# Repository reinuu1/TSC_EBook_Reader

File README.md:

# 📘 TSC_EBook_Reader

## 👨‍💻 Proiect realizat de: DINU Andrei-Marian  
### 📚 Pentru cursul: Teoria Sistemelor de Calcul, 2025  

---

## 🔍 Descriere generală

**OpenBook** este un e-reader open-source, construit în jurul microcontrollerului **ESP32-C6**.  
Acesta dispune de:

- Display **E-Ink 7.5"**
- Baterie **Li-Po**
- Stocare **microSD**
- Senzori de mediu (**BME688**)
- Modul RTC (**DS3231**)

---

## Mapping pini ESP32-C6

| Semnal        | ESP32 Pin | Funcție                      |
|---------------|-----------|------------------------------|
| EPD_BUSY      | IO3       | Status display               |
| EPD_RST       | IO23      | Reset display                |
| EPD_DC        | IO5       | Data/Command                 |
| EPD_CS        | IO10      | SPI CS pentru e-paper        |
| EPD_CLK       | IO6       | SPI Clock                    |
| EPD_MOSI      | IO7       | SPI Data Out                 |
| SS_SD         | IO4       | SD Card CS                   |
| SD_MISO       | IO2       | SPI MISO                     |
| I2C_SDA       | IO21      | RTC + BME688                 |
| I2C_SCL       | IO22      | RTC + BME688                 |
| RTC_RST       | IO18      | Reset DS3231                 |
| RTC_INT       | IO0       | Interrupt RTC                |
| 32KHz_CLK     | IO1       | Oscilator RTC                |
| IO/BOOT Btn   | IO9       | Boot                         |
| IO/CHANGE Btn | IO15      | Navigare                     |
| RESET         | EN        | Reset MCU                    |

## Microcontroller: ESP32-C6-WROOM-1

- **Arhitectură:** RISC-V 32-bit @ 160 MHz  
- **Memorie:** 320KB ROM, 512KB SRAM  
- **Conectivitate:** Wi-Fi 6 (2.4GHz), Bluetooth 5.0  
- **Consum:** ~10mA activ, ~160μA deep sleep  

**Interfețe utilizate:**
- **SPI** – e-paper, microSD, memorie Flash
- **I2C** – RTC, senzor de mediu
- **GPIO** – butoane, LED, semnale control

## 🖥️ Display: Waveshare 7.5" e-Ink V2

- **Rezoluție:** 800x480 px  
- **Interfață:** SPI  
- **Consum:** ~1.2mW activ, ~0.1mW standby

## 🔋 Alimentare

- **Baterie:** Li-Po 1800–2500mAh  
- **Încărcător:** MCP73831  
- **Regulator:** XC6221 LDO 3.3V  

**Protecții integrate:**

- Diodă Schottky – polaritate inversă  
- Varistor ESD – protecție USB  
- Supercapacitor – buffering boot/flash  

**Conectare la ESP32-C6:**

IO7 → MOSI
IO6 → SCK
IO10 → CS
IO5 → DC
IO23 → RST
IO3 → BUSY

## Stocare: MicroSD + SPI Flash
### microSD (până la 32GB FAT32)

IO4 → CS_SD
IO2 → MISO
IO7 → MOSI (partajat)
IO6 → SCK (partajat)
Flash SPI externă (Winbond W25Q64JV – 64Mb)
IO11 → CS
IO2, IO6, IO7 partajați

##  Senzor Mediu: Bosch BME688
- Măsoară: temperatură, umiditate, presiune, compuși gazoși  
- **Consum:** ~3.6mA activ, ~0.1μA sleep  
- **Interfață:** I2C  

**Conectare:**

IO21 → SDA
IO22 → SCL
IO19 → VDDIO (enable senzor)

## RTC: DS3231

- **Precizie:** ±2ppm, compensat termic  
- **Backup:** funcționează pe baterie  
- **Consum:** ~1.5μA backup, ~0.1μA sleep 

**Conectare:**

IO21 → SDA
IO22 → SCL
IO18 → RST
IO0 → INT/SQW
IO1 → 32KHz Clock Out

## ⚡ Estimare consum

| Modul       | Activ (mA) | Sleep (μA) |
|-------------|------------|------------|
| ESP32-C6    | ~10        | ~160       |
| Display     | ~1.2       | ~0.1       |
| microSD     | ~50        | ~10        |
| BME688      | ~3.6       | ~0.1       |
| RTC         | ~0.0015    | ~0.0001    |
| **Total**   | **~65mA**  | **~170μA** |

## Interfață utilizator
- 3 Butoane tactile (TS-1187A):

IO9 → BOOT
IO15 → CHANGE
EN → RESET

- LED status: GPIO + rezistor pull-down  
- Feedback: control simplu via GPIO 

## Alte componente

- **Conector FPC:** Hirose FH34SRJ-24S  
- **Test Pads:** silkscreen pentru depanare  
- **Qwiic/I²C Header:** pentru extensii viitoare 

Observații finale
Toate comunicațiile SPI sunt partajate pe același bus, controlate prin CS separat.

Designul este gândit pentru eficiență energetică și poate funcționa zeci de ore în standby.

Tot sistemul este gândit pentru a fi reproductibil și open-source, ușor de extins cu alte module I²C sau SPI

##  Design Decizii & Trade-offs

-  Alegere ESP32-C6: conectivitate & suport FreeRTOS  
-  E-paper pentru consum redus  
-  Un singur bus SPI (cu CS dedicat pentru SD și e-paper)  
-  GPIO-uri simple pentru butoane

## Debug & Testare

-  Verificare DRC (JLCPCB .dru)  
-  Alimentare testată cu Li-Po + charging  
-  Interfețe SPI & I2C testate cu logic analyzer  
-  Consumul în deep sleep confirmat < 200μA

##  Datasheet-uri & Linkuri componente

|                 Componentă                |                                                     Link Datasheet                                                            |                                                          LINK                                                                           |
|-------------------------------------------|-------------------------------------------------------------------------------------------------------------------------------|-----------------------------------------------------------------------------------------------------------------------------------------|
| USB Connector 112A-TAAR-R03               | [ESP32-C6-WROOM-1](https://www.attend.com.tw/data/download/file/112A-TAAR-R03_Spec.pdf)                                       | [Status display](https://www.digikey.com/en/products/detail/attend-technology/112A-TAAR-R03/17633923)                                   |
| Inductor 68uH (Würth)                     | [7.5" V2 e-Paper](https://www.we-online.com/components/products/datasheet/784373170680.pdf)                                   | [Reset display ](https://eu.mouser.com/ProductDetail/Wurth-Elektronik/784373170680?qs=sGAEpiMZZMv126LJFLh8yzGkpireax1GgDeN9GF1EUQ%3D)   |
| LED Bridgelux                             | [DS3231](https://www.bridgelux.com/sites/default/files/resource_media/DS51_Rev%20F%20Bridgelux%20SMD%203030%20Data%20sheet.pdf)  | [Data/Command](https://www.digikey.com/en/products/detail/bridgelux/BXEM-27E0000-0-000/6618599)                                      |
| Voltage Detector BD5229G                  | [BME688 ](https://fscdn.rohm.com/en/products/databook/datasheet/ic/power/voltage_detector/bd52xxg-e.pdf)                      | [SPI CS pentru e-paper        ](https://www.digikey.com/en/products/detail/rohm-semiconductor/BD5229G-TR/658502)                        |
| Butoane TL3315                            | [XC6221B331MR-G](https://fscdn.rohm.com/en/products/databook/datasheet/ic/power/voltage_detector/bd52xxg-e.pdf)               | [SPI Clock                    ](https://www.digikey.com/en/products/detail/rohm-semiconductor/BD5229G-TR/658502)                        |
| Supercapacitor 0.011F 3.3V                | [MCP73831T-2ACI/OT ](https://mm.digikey.com/Volume0/opasdata/d220001/medias/docus/6537/rev05-CPHCPM.pdf)                      | [SPI Data Out                ](https://www.digikey.com/en/products/detail/seiko-instruments/cph3225a/8692444)                           |
| RTC DS3231SN                              | [LP584174 (1800mAh) ](https://www.analog.com/media/en/technical-documentation/data-sheets/DS3231.pdf)                         | [SD Card CS ](https://www.digikey.com/en/products/detail/analog-devices-inc-maxim-integrated/DS3231SN/1197576)                          |
| Capacitor 0402YD104MAT2A                  | [FH34SRJ-24S-0.5SH(50)](https://eu.mouser.com/datasheet/2/40/cx5r_KGM-3223198.pdf)                                            | [SPI MISO                  ](https://eu.mouser.com/ProductDetail/KYOCERA-AVX/0402YD104MAT2A?qs=4PckX6MNpMErOINbbZj3Cw%3D%3D)            |
| ESP32-C6-WROOM-1-N8                       | [W25Q64JV             ](https://www.espressif.com/sites/default/files/documentation/esp32-c6-wroom-1_wroom-1u_datasheet_en.pdf)  | [RTC + BME688                ](https://www.digikey.com/en/products/detail/espressif-systems/ESP32-C6-WROOM-1-N8/17728866)            |
| Varistor USB PFMF.050.2                   | [Molex 104031-0811     ](https://ro.mouser.com/datasheet/2/358/typ_PFMF-1275918.pdf)                                          | [RTC + BME688               ](https://ro.mouser.com/ProductDetail/Schurter/PFMF.050.2?qs=1auRipcfynCums5v1iucSA%3D%3D)                  |
| DiodA Schottky SD0805S020S1R0             | [USB4110-GF-A           ](https://datasheets.kyocera-avx.com/schottky.pdf)                                                    | [Reset DS3231                ](https://www.digikey.com/en/products/detail/kyocera-avx/sd0805s020s1r0/3749517)                           |
| Senzor BME680                             | [SS14                  ](https://www.bosch-sensortec.com/media/boschsensortec/downloads/datasheets/bst-bme680-ds001.pdf)      | [ Interrupt RTC  ](https://www.digikey.com/en/products/detail/bosch-sensortec/bme680/7401317)                                           |
| Rezistori SMD 0402                        | [PFMF05S050T2          ](https://www.yageo.com/upload/media/product/products/datasheet/rchip/PYu-RC_Group_51_RoHS_L_12.pdf)   | [Oscilator RTC ](https://www.digikey.com/en/products/detail/yageo/RC0402JR-07100KL/726416)                                              |
| P-MOS DMG2305UX-7                         | [TS-1187A-B-A-B        ](https://www.diodes.com/assets/Datasheets/DMG2305UX.pdf)                                              | [Boot                        ](https://www.digikey.com/en/products/detail/diodes-incorporated/DMG2305UX-7/4340667)                      |
| MCP73831T (Charger IC)                    | [RC0402FR-07100KL       ](https://ww1.microchip.com/downloads/en/DeviceDoc/MCP73831-Family-Data-Sheet-DS20001984H.pdf)        | [Navigare   ](https://www.digikey.com/en/products/detail/microchip-technology/MCP73831T-2ACI-OT/964301)                                 |
| Hirose FH34SRJ-24S-0.5SH                  | [GRM155R61A105KE15D    ](https://ro.mouser.com/datasheet/2/185/FH34SRJ_24S_0_5SH_99__CL0580_1255_6_99_2DDrawing_0-1615044.pdf)| [Reset MCU                   ](https://ro.mouser.com/ProductDetail/Hirose-Connector/FH34SRJ-24S-0.5SH99?qs=vcbW%252B4%252BSTIpKBl5ap9J8Fw%3D%3D) |
| Battery Monitor MAX17048                  | https://www.analog.com/media/en/technical-documentation/data-sheets/max17048-max17049.pdf                                     | https://www.digikey.com/en/products/detail/analog-devices-inc-maxim-integrated/MAX17048G-T10/3758921                                    |
| Diodă MBR0530                             | https://ro.mouser.com/datasheet/2/258/MBR0520_MBR0580_SOD123_-2492194.pdf                                                     | https://ro.mouser.com/ProductDetail/Micro-Commercial-Components-MCC/MBR0530-TP?qs=KFo7JewZbUECRHkxGanrdg%3D%3D                          |
| ESD Suppressor – PGB1010603MR             | https://www.littelfuse.com/assetdocs/pulseguard-esd-suppressors-pgb1-datasheet?assetguid=8a337998-d54d-466b-be4e-dc5bcd1f9321 | https://www.digikey.com/en/products/detail/littelfuse-inc/PGB1010603MR/715755                                                           |
| Qwiic Connector OM-E-QWIIC                | https://www.sparkfun.com/qwiic                                                                                                | https://www.digikey.com/en/products/detail/onion-corporation/om-e-qwiic/9922970                                                         |
| Capacitor 0.5pF–100uF GCQ1555C1HR50WB01   | https://ro.mouser.com/datasheet/2/281/1/GCQ1555C1HR50WB01_01A-3146956.pdf                                                     | https://ro.mouser.com/ProductDetail/Murata-Electronics/GCQ1555C1HR50WB01D?qs=0lQeLiL1qybSG%2FOlONlvIA%3D%3D                             |
| USB-C Conector USB4110-GF-A               | https://gct.co/files/drawings/usb4110.pdf                                                                                     | https://eu.mouser.com/ProductDetail/GCT/USB4110-GF-A?qs=KUoIvG%2F9IlYiZvIXQjyJeA%3D%3D                                                  |
| Rezistor                                  | https://industrial.panasonic.com/ww/products/pt/general-purpose-chip-resistors/models/ERJ2GE0R00X                             | https://www.digikey.com/en/products/detail/panasonic-electronic-components/ERJ-2GE0R00X/146727                                          |

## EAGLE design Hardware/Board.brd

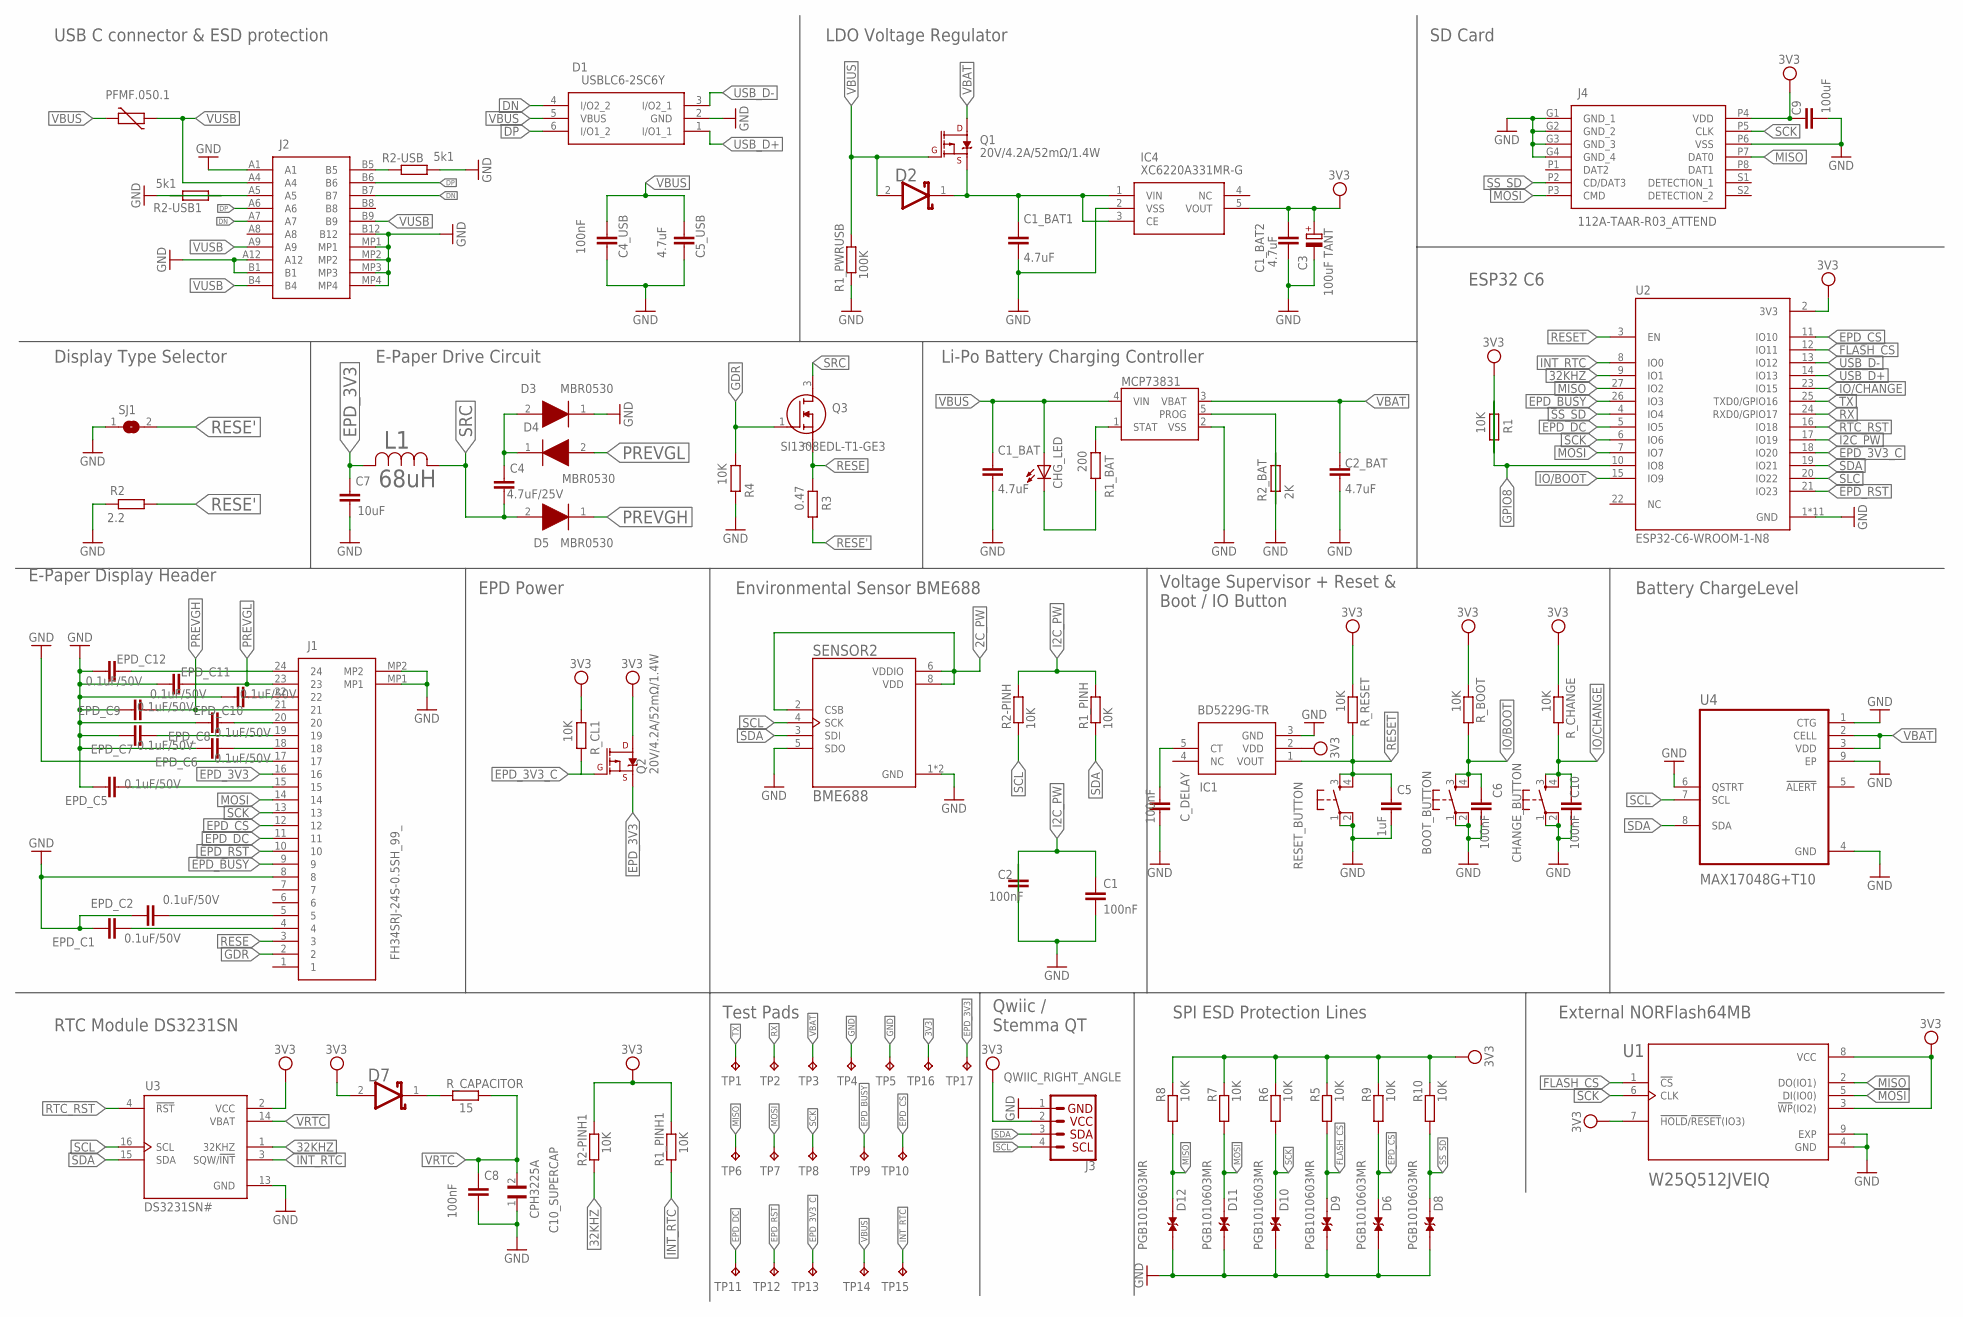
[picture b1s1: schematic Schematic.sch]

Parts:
BOOT_BUTTON: BUTTON_CUSYOMV1; MYBUTTON
C1, C2, C4_USB, C6, C8, C10: 100nF; EAGLE-LTSPICE_C0402
C1_BAT, C1_BAT1, C1_BAT2, C2_BAT, C5_USB: 4.7uF; EAGLE-LTSPICE_C0402
C3: 100uF TANT; RCL_CT3528
C4: 4.7uF/25V; EAGLE-LTSPICE_C0402
C5: 1uF; EAGLE-LTSPICE_C0402
C7: 10uF; EAGLE-LTSPICE_C0402
C9: 100uF; EAGLE-LTSPICE_C0402
C10_SUPERCAP: CPH3225A; CAPCP3225X100N
CHANGE_BUTTON: BUTTON_CUSYOMV1; MYBUTTON
CHG_LED: ADAFRUIT_LEDCHIP-LED0603; ADAFRUIT_CHIP-LED0603
C_DELAY: 100nF; EAGLE-LTSPICE_C0402
D1: USBLC6-2SC6Y; SOT95P280X145-6N
D2, D7: ESP32_WROVER_AVX---SD0805S020S1R0_AVX_SD0805S020S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; ESP32_WROVER_AVX---SD0805S020S1R0_AVX_SD0805S020S1R0_0
D3, D4, D5: MBR0530; SOD3716X135N
D6, D8, D9, D10, D11, D12: PGB1010603MR; DIOC1608X36N
EPD_C1, EPD_C2, EPD_C5, EPD_C6, EPD_C7, EPD_C8, EPD_C9, EPD_C10, EPD_C11, EPD_C12: 0.1uF/50V; EAGLE-LTSPICE_C0402
IC1: BD5229G-TR; SOT95P280X125-5N
IC4: XC6220A331MR-G; SOT95P280X120-5N
J1: FH34SRJ-24S-0.5SH_99_; FH34SRJ24S05SH99
J2: J2; SAMACSYS_PARTS_USB4110GFA
J3: QWIIC_RIGHT_ANGLE; JST04_1MM_RA
J4: 112A-TAAR-R03_ATTEND; 112ATAARR03ATTEND
L1: 68uH; IND_4828-WE-TPC_WRE
MCP73831: ESP32_WROVER_SPARKFUN-IC-POWER_MCP73831; ESP32_WROVER_SPARKFUN-IC-POWER_SOT23-5
PFMF.050.1: ESP32C6_VARISTORCN1812; ESP32C6_VARISTOR_CT/CN1812
Q1, Q2: 20V/4.2A/52mΩ/1.4W; ESP32_WROVER_SPARKFUN-DISCRETESEMI_SOT23-3
Q3: SI1308EDL-T1-GE3; SOT65P210X110-3N
R1, R1_PINH, R1_PINH1, R2-PINH, R2-PINH1, R4, R5, R6, R7, R8, R9, R10: 10K; ESP32_WROVER_EAGLE-LTSPICE_R0402
R1_BAT: 200; ESP32_WROVER_EAGLE-LTSPICE_R0402
R1_PWRUSB: 100K; ESP32_WROVER_EAGLE-LTSPICE_R0402
R2: 2.2; ESP32_WROVER_EAGLE-LTSPICE_R0402
R2-USB, R2-USB1: 5k1; ESP32_WROVER_EAGLE-LTSPICE_R0402
R2_BAT: 2K; ESP32_WROVER_EAGLE-LTSPICE_R0402
R3: 0.47; ESP32_WROVER_EAGLE-LTSPICE_R0402
RESET_BUTTON: BUTTON_CUSYOMV1; MYBUTTON
R_BOOT: 10K; ESP32_WROVER_EAGLE-LTSPICE_R0402
R_CAPACITOR: 15; ESP32_WROVER_EAGLE-LTSPICE_R0402
R_CHANGE: 10K; ESP32_WROVER_EAGLE-LTSPICE_R0402
R_CL1: 10K; ESP32_WROVER_EAGLE-LTSPICE_R0402
R_RESET: 10K; ESP32_WROVER_EAGLE-LTSPICE_R0402
SENSOR2: BME688; ESP32_WROVER_BME680_PSON80P300X300X100-8N
SJ1: SJ
TP1, TP2, TP3, TP4, TP5, TP6, TP7, TP8, TP9, TP10, TP11, TP12, TP13, TP14, TP15, TP16, TP17: TPTP20R; TP20R
U1: W25Q512JVEIQ; SON127P600X800X80-9N
U2: ESP32-C6-WROOM-1-N8; XCVR_ESP32-C6-WROOM-1-N8
U3: DS3231SN#; SOIC127P1032X265-16N
U4: MAX17048G+T10; SON50P200X200X80-9N

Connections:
2C_PW: SENSOR2.2 (CSB), SENSOR2.6 (VDDIO), SENSOR2.8 (VDD)
3V3: C1_BAT2.2, C3.+, C9.2, D7.2 (ANODE), IC1.2 (VDD), IC4.5 (VOUT), J3.2, J4.P4 (VDD), Q2.3 (D), R1.1, R1_PINH1.2, R2-PINH1.2, R5.2, R6.2, R7.2, R8.2, R9.2, R10.2, R_BOOT.1, R_CHANGE.1, R_CL1.2, R_RESET.1, TP16.TP, U1.3 (!WP!(IO2)), U1.7 (!HOLD!/!RESET!(IO3)), U1.8 (VCC), U2.2 (3V3), U3.2 (VCC)
32KHZ: R2-PINH1.1, U2.9 (IO1), U3.1 (32KHZ)
DN: J2.A7
DP: J2.A6
EPD_3V3: C7.1, J1.16, L1.2, Q2.2 (S), TP17.TP
EPD_3V3_C: Q2.1 (G), R_CL1.1, TP13.TP, U2.18 (IO20)
EPD_BUSY: J1.9, TP9.TP, U2.26 (IO3)
EPD_CS: D6.2, J1.12, R9.1, TP10.TP, U2.11 (IO10)
EPD_DC: J1.11, TP11.TP, U2.5 (IO5)
EPD_RST: J1.10, TP12.TP, U2.21 (IO23)
FLASH_CS: D9.2, R5.1, U1.1 (!CS), U2.12 (IO11)
GDR: J1.2, Q3.1 (G), R4.2
GND: BOOT_BUTTON.1, BOOT_BUTTON.2, C1.2, C1_BAT.1, C1_BAT1.1, C1_BAT2.1, C2.2, C2_BAT.1, C3.-, C4_USB.2, C5.2, C5_USB.2, C6.2, C7.2, C8.2, C9.1, C10.2, C10_SUPERCAP.1, CHANGE_BUTTON.1, CHANGE_BUTTON.2, C_DELAY.2, D1.2 (GND), D3.1 (K), D6.1, D8.1, D9.1, D10.1, D11.1, D12.1, EPD_C1.1, EPD_C2.1, EPD_C5.1, EPD_C6.1, EPD_C7.1, EPD_C8.1, EPD_C9.1, EPD_C10.1, EPD_C11.1, EPD_C12.1, IC1.3 (GND), IC4.2 (VSS), J1.8, J1.17, J1.MP1, J1.MP2, J2.A1, J2.A12, J2.B1, J2.B12, J2.MP1, J2.MP2, J2.MP3, J2.MP4, J3.1, J4.G1 (GND_1), J4.G2 (GND_2), J4.G3 (GND_3), J4.G4 (GND_4), J4.P6 (VSS), MCP73831.2 (VSS), R1_PWRUSB.1, R2.2, R2-USB.2, R2-USB1.1, R2_BAT.1, R4.1, RESET_BUTTON.1, RESET_BUTTON.2, SENSOR2.1 (GND), SENSOR2.5 (SDO), SENSOR2.7 (GND), SJ1.1, TP4.TP, TP5.TP, U1.4 (GND), U1.9 (EXP), U2.1 (GND), U2.28 (GND), U2.29_1 (GND), U2.29_2 (GND), U2.29_3 (GND), U2.29_4 (GND), U2.29_5 (GND), U2.29_6 (GND), U2.29_7 (GND), U2.29_8 (GND), U2.29_9 (GND), U3.13 (GND), U4.1 (CTG), U4.4 (GND), U4.6 (QSTRT), U4.9 (EP)
GPIO8: R1.2, U2.10 (IO8)
I2C_PW: R1_PINH.2, R2-PINH.2, U2.17 (IO19)
INT_RTC: R1_PINH1.1, TP15.TP, U2.8 (IO0), U3.3 (SQW/!INT)
IO/BOOT: BOOT_BUTTON.3, BOOT_BUTTON.4, C6.1, R_BOOT.2, U2.15 (IO9)
IO/CHANGE: C10.1, CHANGE_BUTTON.3, CHANGE_BUTTON.4, R_CHANGE.2, U2.23 (IO15)
MISO: D12.2, J4.P7 (DAT0), R8.1, TP6.TP, U1.2 (DO(IO1)), U2.27 (IO2)
MOSI: D11.2, J1.14, J4.P3 (CMD), R7.1, TP7.TP, U1.5 (DI(IO0)), U2.7 (IO7)
unnamed: J2.A5, R2-USB1.2
unnamed: J2.B5, R2-USB.1
unnamed: C4_USB.1, C5_USB.1
unnamed: C4.1, D3.2 (A), D4.1 (K)
unnamed: MCP73831.1 (STAT), R1_BAT.2
unnamed: C1_BAT1.2, D2.1 (CATHODE), IC4.1 (VIN), IC4.3 (CE), Q1.2 (S)
unnamed: CHG_LED.C, R1_BAT.1
unnamed: EPD_C12.2, J1.24
unnamed: MCP73831.5 (PROG), R2_BAT.2
unnamed: C1.1, C2.1
unnamed: C_DELAY.1, IC1.5 (CT)
unnamed: D7.1 (CATHODE), R_CAPACITOR.1
unnamed: EPD_C10.2, J1.22
unnamed: EPD_C8.2, J1.20
unnamed: EPD_C7.2, J1.19
unnamed: EPD_C6.2, J1.18
unnamed: EPD_C5.2, J1.15
unnamed: EPD_C2.2, J1.5
unnamed: EPD_C1.2, J1.4
PREVGH: D5.1 (K), EPD_C9.2, J1.21
PREVGL: D4.2 (A), EPD_C11.2, J1.23
RESE: J1.3, Q3.2 (S), R3.2
RESE': R3.1, SJ1.2
RESET: C5.1, IC1.1 (VOUT), RESET_BUTTON.3, RESET_BUTTON.4, R_RESET.2, U2.3 (EN)
RTC_RST: U2.16 (IO18), U3.4 (!RST)
RX: TP2.TP, U2.24 (RXD0/GPIO17)
SCK: D10.2, J1.13, J4.P5 (CLK), R6.1, TP8.TP, U1.6 (CLK), U2.6 (IO6)
SCL: J3.4, R2-PINH.1, SENSOR2.4 (SCK), U3.16 (SCL), U4.7 (SCL)
SDA: J3.3, R1_PINH.1, SENSOR2.3 (SDI), U2.19 (IO21), U3.15 (SDA), U4.8 (SDA)
SLC: U2.20 (IO22)
SRC: C4.2, D5.2 (A), L1.1, Q3.3 (D)
SS_SD: D8.2, J4.P2 (CD/DAT3), R10.1, U2.4 (IO4)
TX: TP1.TP, U2.25 (TXD0/GPIO16)
USB_D+: D1.1 (I/O1_1), U2.14 (IO13)
USB_D-: D1.3 (I/O2_1), U2.13 (IO12)
VBAT: C2_BAT.2, MCP73831.3 (VBAT), Q1.3 (D), TP3.TP, U4.2 (CELL), U4.3 (VDD)
VBUS: C1_BAT.2, CHG_LED.A, D2.2 (ANODE), MCP73831.4 (VIN), PFMF.050.1.2, Q1.1 (G), R1_PWRUSB.2, TP14.TP
VRTC: C8.1, C10_SUPERCAP.2, R_CAPACITOR.2, U3.14 (VBAT)
VUSB: J2.A4, PFMF.050.1.1

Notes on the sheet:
USB C connector & ESD protection
Display Type Selector
E-Paper Drive Circuit
LDO Voltage Regulator
SD Card
Li-Po Battery Charging Controller
ESP32 C6
E-Paper Display Header
EPD Power
Environmental Sensor BME688
Voltage Supervisor + Reset & Boot / IO Button
Battery ChargeLevel
External NORFlash64MB
RTC Module DS3231SN
Test Pads
Qwiic / Stemma QT
SPI ESD Protection Lines

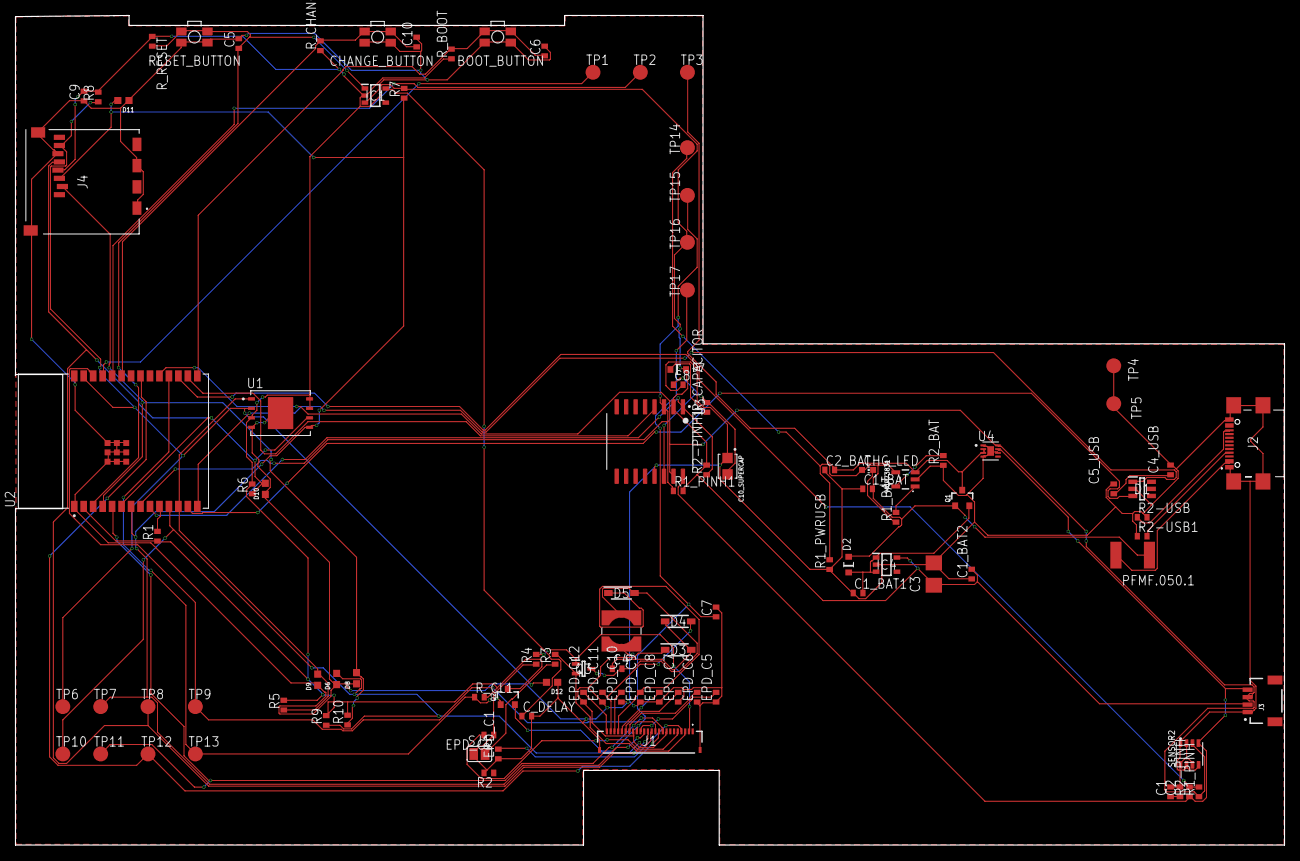
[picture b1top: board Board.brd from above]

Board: 2 copper layers, 170.2 x 111.3 mm, 103 parts (0 on the bottom side), 57 nets.

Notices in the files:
parts and their libraries:
COPYRIGHT: Copyright (C) 2024 Ultra Librarian. All rights reserved.
